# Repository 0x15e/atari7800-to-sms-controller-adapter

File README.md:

# Atari 7800 to Sega Master System Controller Adapter

## Summary

I designed this adapter so that I could use an original Atari 7800 Proline joystick with my Daemonbite Sega USB adapter on MiSTer. It adapts the pinout and logic to that of a Sega Master System controller, allowing it to work with more commonly available Sega adapters and, in theory, an actual Sega Master System or Genesis (untested). The left trigger functions as button 1 and the right as button 2.

It should be noted that because this adapter operates the controller in 7800 mode full time, the single-button backwards compatible mode is not supported.

## Background

When designing the Atari 7800's joystick, Atari chose to make it backwards compatible with the 2600 in such a way that both buttons trigger the same fire button pin that the 2600 uses. Unfortunately for anyone wanting to use the stick for something besides the 2600 or 7800, they did it in such a way that the pinout is incompatible with other, more "standard", multi-button controllers.

The controllers function as such:

**2600 Mode**: Both fire buttons trigger the same fire button pin that the 2600 uses and are active low.

**7800 Mode**: 5V is fed to the 2600 fire button pin and the separate fire buttons are held low by pulldowns internal to the controller. Pressing a button pulls its pin high (which is the opposite of how most controllers work).

At best, connecting a 7800 controller to an adapter or system not designed for it causes the buttons to activate the same pin. At worst, something could be damaged by the non-standard wiring in the controller.

## Implementation

This adapter uses two 2n4401 transistors to change the buttons from active-high to active-low, and reroutes the pins to the correct locations for a Master System controller. The base and collector resistor values were chosen in an attempt to match the values inside a 7800 system as closely as possible (based on the information [here](https://www.retronicdesign.com/en/specifications/atari-7800-joystick/)).

## Required Components

- 1x adapter PCB from the fab of your choice (currently shared on [OSH Park](https://oshpark.com/shared_projects/y2CrC8d0) for convenience)
- 2x 2n4401 NPN transistors (or suitable replacements)
- 2x 1.8KΩ resistors (R1,R2) (1/8W is fine, SMD or through-hole)
- 2x 270Ω resistors (R3,R4) (1/8W is fine, SMD or through-hole)
- 1x DE-9 Male connector w/ solder cup termination (J1)
- 1x DE-9 Female connector w/ solder cup termination (J2)
- 1x Gender changer hood (this adapter is known to fit into [this one sold by SF Cable](https://www.sfcable.com/db9-to-db9-gender-changer-hood.html))

I used the DE-9 connectors from [this package](https://www.amazon.com/gp/product/B07C6W5TJ9/), which comes with 10 male / female pairs.

## Assembly

All of the component locations are marked on the PCB to make assembly as quick and easy as possible.

1. Place and solder the resistors (1.8KΩ at R1 and R2, 270Ω at R3 and R4).
2. Place and solder the transistors. Make sure they sit as close to the board as the flats on the legs will allow and that their orientation matches the markings on the PCB. If you don't get them low enough, there may not be enough clearance inside the gender changer hood. When they're right, everything will fit without having to bend them to the side.
3. Position the male and female DE-9 connectors on the appropriate ends of the PCB and carefully place the assembly in half of the gender changer hood. Make sure that the solder cups on the connectors line up with the pads on the PCB and that everything sits comfortably inside the gender changer hood and that they are as perpendicular to the PCB as possible.
4. Solder **one** pin on each DE-9 connector to tack things in place. I recommend using one of the middle pins and moving quickly as the gender changer hood isn't meant for high temperatures and may melt.
5. Test fit the gender changer hood to make sure the tabs on the DE-9 connectors line up correctly with the slots in the gender changer hood, and to verify clearance for the transistors.
6. Remove the hood and finish soldering the rest of the pins on the DE-9 connectors.
7. Put everything back in the hood.

## Disclaimer

This adapter is offered without any support or warranty for any purpose. It works well for my intended purpose (adapting the controller to work with a [Daemonbite adapter](https://github.com/MickGyver/DaemonBite-Retro-Controllers-USB)) but I take no responsibility if it doesn't work for you, breaks something, or says mean things to your cat.

## License

This adapter is licensed as CC0 1.0 Universal. Do with it as you please.

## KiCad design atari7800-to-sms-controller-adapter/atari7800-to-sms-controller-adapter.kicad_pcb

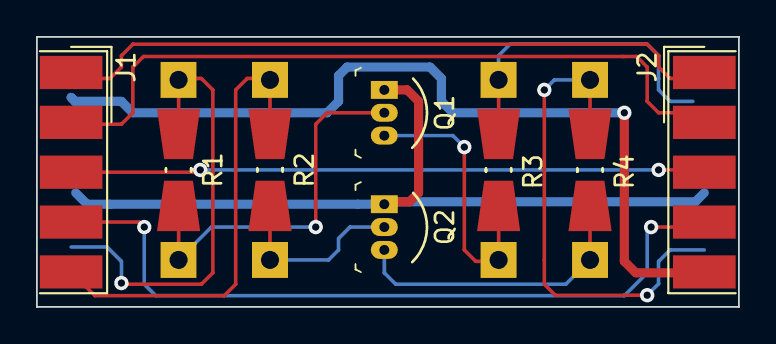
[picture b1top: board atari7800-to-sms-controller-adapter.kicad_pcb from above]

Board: 2 copper layers, 39.0 x 15.0 mm, 8 parts (0 on the bottom side), 14 nets.

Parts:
J1: DB9_Male; DSUB-9_Male_EdgeMount_P2.77mm
J2: DB9_Female; DSUB-9_Female_EdgeMount_P2.77mm
Q1, Q2: 2N4401; TO-92-3
R1, R2: 1.8K; Resistor_SMD+THTuniversal_0805to1206_RM10_HandSoldering_Rev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
R3, R4: 270; Resistor_SMD+THTuniversal_0805to1206_RM10_HandSoldering_Rev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

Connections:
/DOWN: J1.2, J2.2
/FIRE1: J2.6, R3.1
/FIRE2: J2.9, R4.1
/LEFT: J1.3, J2.3
/L_FIRE: J1.9, R1.2
/RIGHT: J1.4, J2.4
/R_FIRE: J1.5, R2.2
/UP: J1.1, J2.1
/Vcc: J1.6, J2.5
GND: J1.8, J2.8, Q1.1, Q2.1
unnamed: Q1.2, R1.1
unnamed: Q1.3, R3.2
unnamed: Q2.2, R2.1
unnamed: Q2.3, R4.2

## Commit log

2021-04-20 Initial commit (1.0)

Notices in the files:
atari7800-to-sms-controller-adapter/atari7800-to-sms-controller-adapter.kicad_pcb:
Licensed under CC0 1.0 Universal
